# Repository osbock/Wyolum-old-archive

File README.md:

# Wyolum-old-archive aka the google code clockthree repo
This is an archive of the old Wyolum Google code repo.
New commits should not be made here.
See instead separate repositories under:
http://github.com/wyolum

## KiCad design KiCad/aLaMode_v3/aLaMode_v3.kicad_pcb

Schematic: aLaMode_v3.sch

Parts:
C1, C7, C14: 100n; c_0805
C8: 47u,10V; C_ELCO_SMD
C10, C11: 22p; c_0805
D3, D4: RB886G; d_VMD2
D8: MBRM110LT1G; do_457
DIP1: DIP
F2: nanoSMDC110F; f_1206
IC1: ATMEGA328-PU; DIP-28__300_ELL
P4: PWM_SERVO; Header_Servo
P5: 5V_SERVO; Header_Servo
P6: GND_SERVO; Header_Servo
P7: GPS_UP501; Header_GPS
P8: FTDI; Header_FTDI
P9: ICSP; Header_ICSP
P13: AREF; Header_A_REF
P14: ANALOG_5V0; Header_6x1
P15: ANALOG_GND; Header_6x1
R1, R2, R3, R4, R6, R7: 10k; r_0805
R15: 8k2; r_0805
R16: 16k; r_0805
SD1: SD_CARD_MICRO; SD_Micro
SHIELD1: ARDUINO_SHIELD; ARDUINO_SHIELD_2_040pins
SW1: RST; SW_SMD
U2: 74HC125; SO14E
X1: 16MHz; Xtal_SMD2

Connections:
+3.3V: C14.2, D3.1 (A), P7.4, P13.1, P14.4, P14.5, P14.6, R3.1, R4.1, R6.1, SD1.4, SHIELD1.3V3, U2.12 (D), U2.13 (E), U2.14 (VCC); also elsewhere on the board
/5V_INT: F2.2, P4.7, P4.8
/5V_SERVO: C8.1, D8.2 (K), P5.1, P5.2, P5.3, P5.4, P5.5, P5.6, P5.7, P5.8
/AREF: IC1.21 (AREF), P13.2, SHIELD1.AREF
/GPS_BAT: D3.2 (K), D4.2 (K), P7.5
/GPS_Rx: P7.1, R15.2, R16.1
/PB0: IC1.14 (PB0(ICP)), SHIELD1.8
/PB1: IC1.15 (PB1(OC1A)), P4.4, SHIELD1.9
/PB6: C10.1, IC1.9 (PB6(XTAL1/TOSC1)), X1.1
/PB7: C11.1, IC1.10 (PB7(XTAL2/TOSC2)), X1.2
/PC0: IC1.23 (PC0(ADC0)), SHIELD1.AD0
/PC1: IC1.24 (PC1(ADC1)), SHIELD1.AD1
/PC2: IC1.25 (PC2(ADC2)), SHIELD1.AD2
/PC3: IC1.26 (PC3(ADC3)), SHIELD1.AD3
/PD2_1pps: IC1.4 (PD2(INT0)), P7.6, SHIELD1.2
/PD4_GPS_Rx: IC1.6 (PD4(XCK/T0)), R15.1, SHIELD1.4
/PD5: IC1.11 (PD5(T1)), P4.2, SHIELD1.5
/PD6_GPS_Tx: IC1.12 (PD6(AIN0)), P4.3, P7.2, SHIELD1.6
/PD7: IC1.13 (PD7(AIN1)), SHIELD1.7
/RPi/5V0: C1.1, F2.1, IC1.7 (VCC), IC1.20 (AVCC), P9.2, P13.3, P14.1, P14.2, P14.3, R1.1, R2.1, R7.1, SHIELD1.5V; also elsewhere on the board
/RPi/MISO: IC1.18 (PB4(MISO)), P9.1, SD1.7, SHIELD1.12; also elsewhere on the board
/RPi/MOSI: IC1.17 (PB3(MOSI/OC2)), P4.6, P9.4, R4.2, SHIELD1.11, U2.5 (D); also elsewhere on the board
/RPi/RESET: C7.2, IC1.1 (PC6(/RESET)), P9.5, R7.2, SHIELD1.RST, SW1.2; also elsewhere on the board
/RPi/RXD: IC1.2 (PD0(RXD)), P8.4, SHIELD1.0; also elsewhere on the board
/RPi/SCK: IC1.19 (PB5(SCK)), P9.3, R6.2, SHIELD1.13, U2.2 (D); also elsewhere on the board
/RPi/SCL: IC1.28 (PC5(ADC5/SCL)), R1.2, SHIELD1.AD5; also elsewhere on the board
/RPi/SDA: IC1.27 (PC4(ADC4/SDA)), R2.2, SHIELD1.AD4; also elsewhere on the board
/RPi/TXD: IC1.3 (PD1(TXD)), P8.5, SHIELD1.1; also elsewhere on the board
/SD_CLK: SD1.5, U2.3 (O)
/SD_CS: SD1.2, U2.8 (O)
/SD_DATA_IN: SD1.3, U2.6 (O)
/SS: IC1.16 (PB2(SS/OC1B)), P4.5, R3.2, SHIELD1.10, U2.9 (D)
/aLaMode_pwr/USBVCC: P8.3; also elsewhere on the board
/aLaMode_pwr/V_IN: SHIELD1.V_IN; also elsewhere on the board
/aLaMode_rtc/BAT: D4.1 (A); also elsewhere on the board
/aLaMode_rtc/PD3_SQW: IC1.5 (PD3(INT1)), P4.1, SHIELD1.3; also elsewhere on the board
/~RTS: C7.1, P8.6
GND: C1.2, C8.2, C10.2, C11.2, C14.1, D8.1 (A), IC1.8 (GND), IC1.22 (AGND), P6.1, P6.2, P6.3, P6.4, P6.5, P6.6, P6.7, P6.8, P7.3, P8.1, P8.2, P9.6, P15.1, P15.2, P15.3, P15.4, P15.5, P15.6, R16.2, SD1.6, SD1.G1, SD1.G2, SD1.G3, SD1.G4, SHIELD1.GND1, SHIELD1.GND2, SHIELD1.GND3, SW1.1, U2.1 (E), U2.4 (E), U2.7 (GND), U2.10 (E); also elsewhere on the board

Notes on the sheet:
PD3 (SQW) RTC 1Hz signal
FTDI Header
ISP Header
EXT Mode : Connect EXT Servo supply to 5V_Servo and GND_SERVO Connectors Pins 7/8. INT Mode : Use jumper links to shunt Pins 7/8 of PWM_SERVO and 5V_SERVO connectors to run Servos using on board 5V.
SERVO Header
PWM6
PWM5
PWM4
PWM3
PWM2
PWM1
GPS Header
PD2 (1pps) GPS 1pps signal
5V to 3V level translation for GPS Rx signal. R16 may be replaced with 3V3 Zener Diode.

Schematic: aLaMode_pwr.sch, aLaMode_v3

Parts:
C2, C4: 100n; c_0805
C3: 2u2 Tant; c_0805
C5: 2u2; c_0805
C6: 100u,25V; C_ELCO_SMD
C15: 1n; c_0805
C16: 10n; c_0805
D1: 5V0; led_0805
D2: 3V3; led_0805
D5: MBRM110LT1G; do_457
D7: SMBJ5.0CA-TR; diode-DO214AA
D13: BLINK; led_0805
F1: nanoSMDC110F; f_1206
G1, G2: Logo_Wyolum; Logo-WL3
G3, G4: Logo_OH; OSHW_6mm
P10: V_IN; JACK_ALIM
P12: UUSB_B; USB_B_Micro
PCB1: PCB
Q1: FDN340P; SOT23-3
R5, R8: 1k5; r_0805
R10, R11: 10k; r_0805
R12: 1k; r_0805
R14: 0E; r_0805
U1: LP2985-33DBVR; SOT23-5
U3: NCP1117ST50T3G; SOT223
U5: LM358N; SO8E

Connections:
+3.3V: C5.1, R8.1, U1.5 (OUT), U5.2 (-); also elsewhere on the board
/RPi/5V0: C2.1, C3.1, C4.1, C15.1, D7.1, F1.2, Q1.S, R5.1, R14.2, U1.1 (IN), U1.3 (ON/~OFF), U3.2 (OUT), U3.4 (OUT), U5.8 (VCC); also elsewhere on the board
/RPi/SCK: U5.5 (+); also elsewhere on the board
/aLaMode_pwr/CMP: R10.2, R11.1, U5.3 (+)
/aLaMode_pwr/GATE_CMD: Q1.G, U5.1
/aLaMode_pwr/PWR_IN: D5.1 (A), P10.1 (+)
/aLaMode_pwr/USBVCC: Q1.D; also elsewhere on the board
/aLaMode_pwr/USB_IN: F1.1, P12.1 (5V_USB)
/aLaMode_pwr/V_IN: C6.1, D5.2 (K), R10.1, R14.1, U3.3 (IN); also elsewhere on the board
GND: C2.2, C3.2, C4.2, C5.2, C6.2, C15.2, C16.2, D1.2 (K), D2.2 (K), D7.2, D13.2 (K), P10.2 (-), P10.3 (S), P12.5 (GND), P12.T1, P12.T2, P12.T3, P12.T4, P12.T5, P12.T6, R11.2, U1.2 (GND), U3.1 (GND), U5.4 (GND); also elsewhere on the board
unnamed: C16.1, U1.4 (NC/FB)
unnamed: D1.1 (A), R5.2
unnamed: D13.1 (A), R12.2
unnamed: R12.1, U5.6 (-), U5.7
unnamed: D2.1 (A), R8.2

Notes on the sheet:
INDICATORS
BLINK LED - D13
USB<->Barrel Socket Auto Switch
BARREL POWER SOCKET
Micro USB-B POWER SOCKET
If using Micro USB -B socket, DO NOT INSTALL : P10, D5, U3 AND INSTALL Resistor R14 across pins 2 and 3 of U3 If using Barrel Socket, DO NOT INSTALL : P12, F1, D7, C15, R14
TE - 1981568-1 or FCI - 10118193-0001LF
Bi-directional clamping Diode, 5V
Polyswitch resettable fuse 1.1A Hold, 2.2A Trip 8V max.
DNP

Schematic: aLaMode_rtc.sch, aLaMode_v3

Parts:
B2, B3, B15: I/O
BT1: BATT_RTC; CR1632_2
C9: 100n; c_0805
R9: 10k; r_0805
U4: DS3231N; DS3231

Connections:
/RPi/5V0: R9.1, U4.2 (Vcc); also elsewhere on the board
/RPi/SCL: U4.16 (SCL); also elsewhere on the board
/RPi/SDA: U4.15 (SDA); also elsewhere on the board
/aLaMode_rtc/32k: B15.1, U4.1 (32KHz)
/aLaMode_rtc/BAT: BT1.+, C9.1, U4.14 (Vbat); also elsewhere on the board
/aLaMode_rtc/PD3_SQW: B2.1, R9.2, U4.3 (!(INT)/SQR); also elsewhere on the board
/aLaMode_rtc/RST: B3.1, U4.4 (!(Reset))
GND: BT1.-, C9.2, U4.5 (NC), U4.6 (NC), U4.7 (NC), U4.8 (NC), U4.9 (NC), U4.10 (NC), U4.11 (NC), U4.12 (NC), U4.13 (GND); also elsewhere on the board

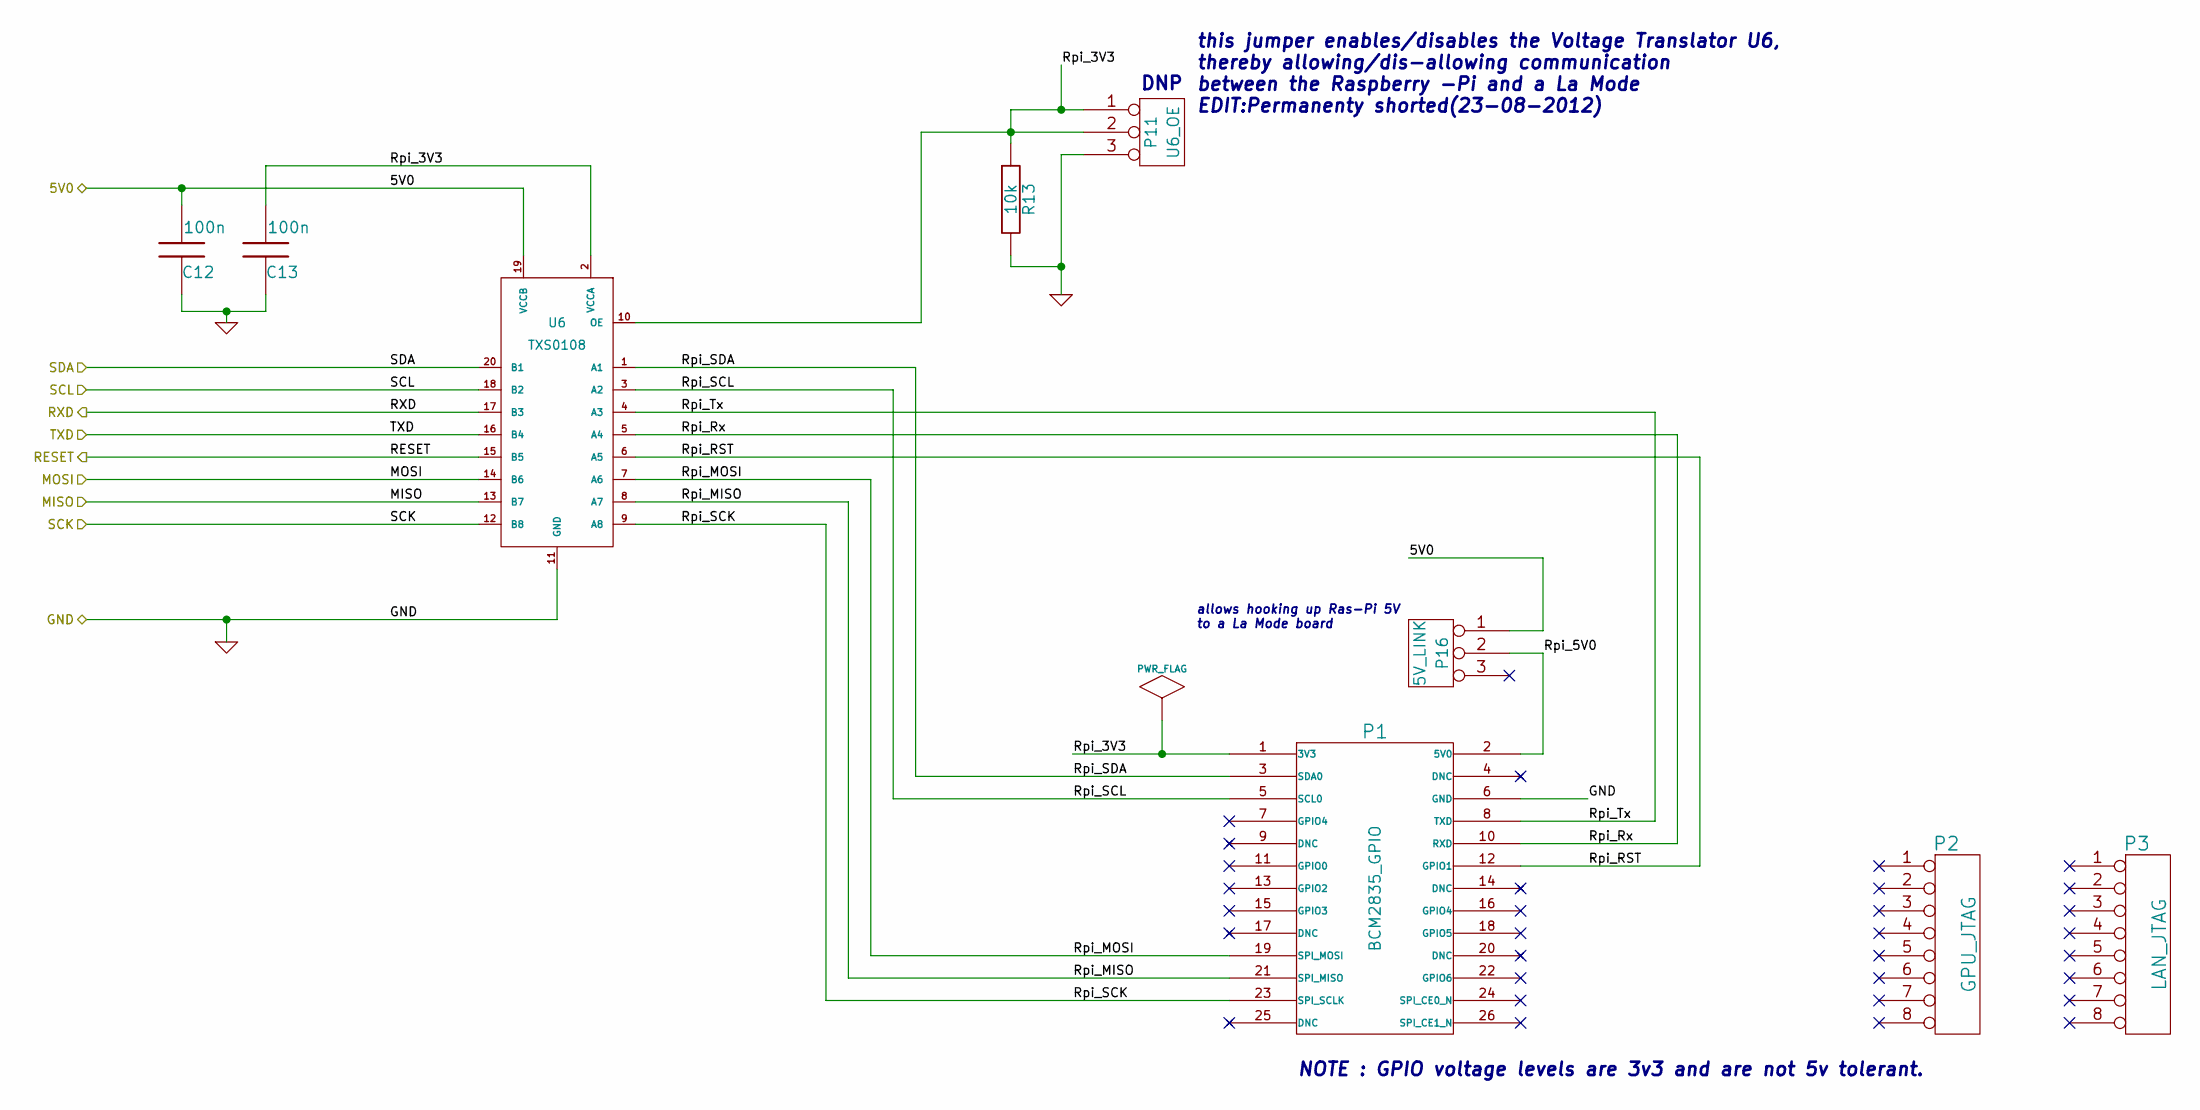
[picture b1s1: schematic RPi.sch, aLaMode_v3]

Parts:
C12, C13: 100n; c_0805
P1: BCM2835_GPIO; Header_GPIO
P2: GPU_JTAG; Header_GPU_JTAG
P3: LAN_JTAG; Header_GPU_JTAG
P11: U6_OE; Header_U6OE_SMT
P16: 5V_LINK; Header_U6OE_SMT
R13: 10k; r_0805
U6: TXS0108; tssop-20

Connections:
/RPi/5V0: C12.2, P16.1, U6.19 (VCCB); also elsewhere on the board
/RPi/MISO: U6.13 (B7); also elsewhere on the board
/RPi/MOSI: U6.14 (B6); also elsewhere on the board
/RPi/RESET: U6.15 (B5); also elsewhere on the board
/RPi/RXD: U6.17 (B3); also elsewhere on the board
/RPi/Rpi_3V3: C13.2, P1.1 (3V3), P11.1, P11.2, R13.1, U6.2 (VCCA), U6.10 (OE)
/RPi/Rpi_5V0: P1.2 (5V0), P16.2
/RPi/Rpi_MISO: P1.21 (SPI_MISO), U6.8 (A7)
/RPi/Rpi_MOSI: P1.19 (SPI_MOSI), U6.7 (A6)
/RPi/Rpi_RST: P1.12 (GPIO1), U6.6 (A5)
/RPi/Rpi_Rx: P1.10 (RXD), U6.5 (A4)
/RPi/Rpi_SCK: P1.23 (SPI_SCLK), U6.9 (A8)
/RPi/Rpi_SCL: P1.5 (SCL0), U6.3 (A2)
/RPi/Rpi_SDA: P1.3 (SDA0), U6.1 (A1)
/RPi/Rpi_Tx: P1.8 (TXD), U6.4 (A3)
/RPi/SCK: U6.12 (B8); also elsewhere on the board
/RPi/SCL: U6.18 (B2); also elsewhere on the board
/RPi/SDA: U6.20 (B1); also elsewhere on the board
/RPi/TXD: U6.16 (B4); also elsewhere on the board
GND: C12.1, C13.1, P1.6 (GND), P11.3, R13.2, U6.11 (GND); also elsewhere on the board

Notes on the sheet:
allows hooking up Ras-Pi 5V to a La Mode board
this jumper enables/disables the Voltage Translator U6, thereby allowing/dis-allowing communication between the Raspberry -Pi and a La Mode EDIT:Permanenty shorted(23-08-2012)
NOTE : GPIO voltage levels are 3v3 and are not 5v tolerant.
DNP

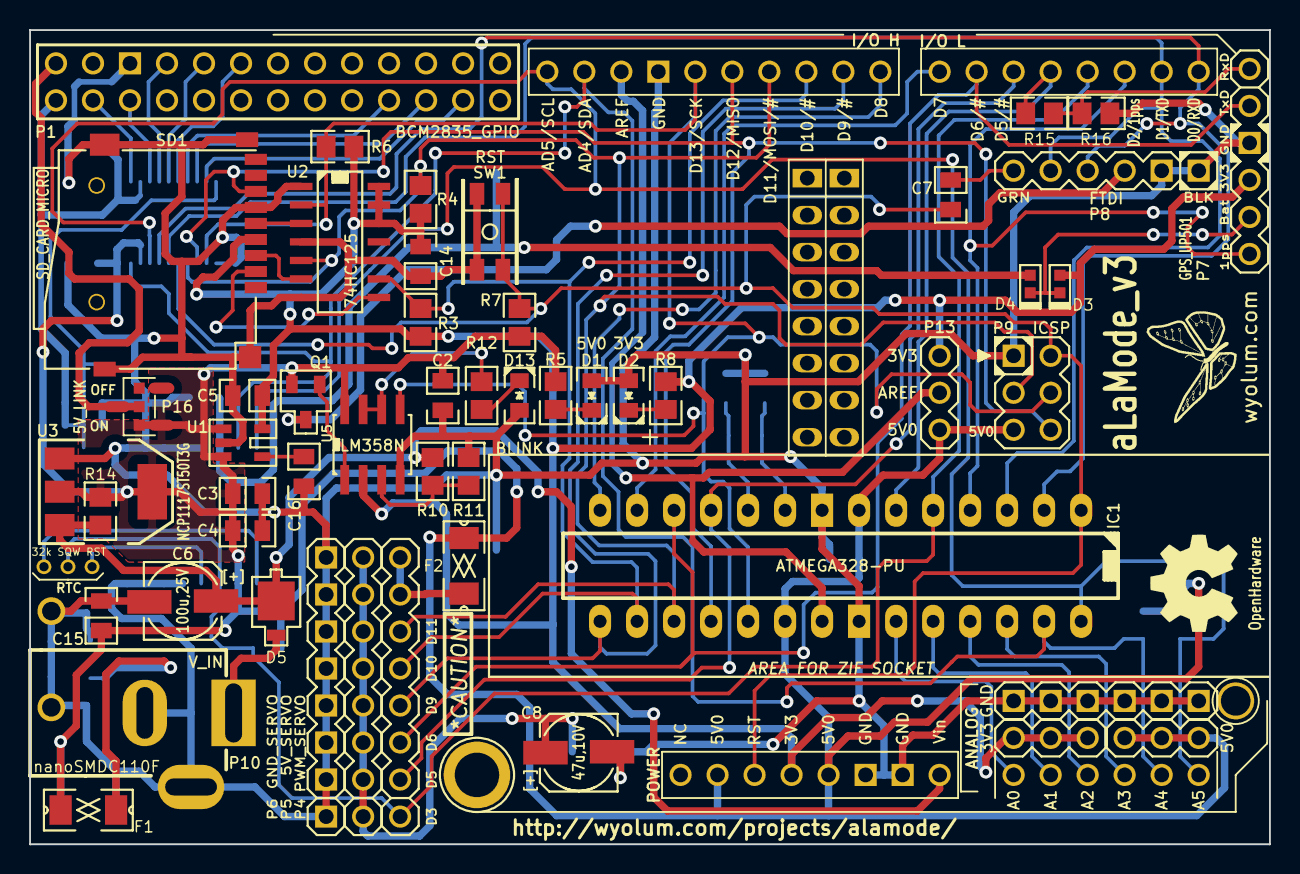
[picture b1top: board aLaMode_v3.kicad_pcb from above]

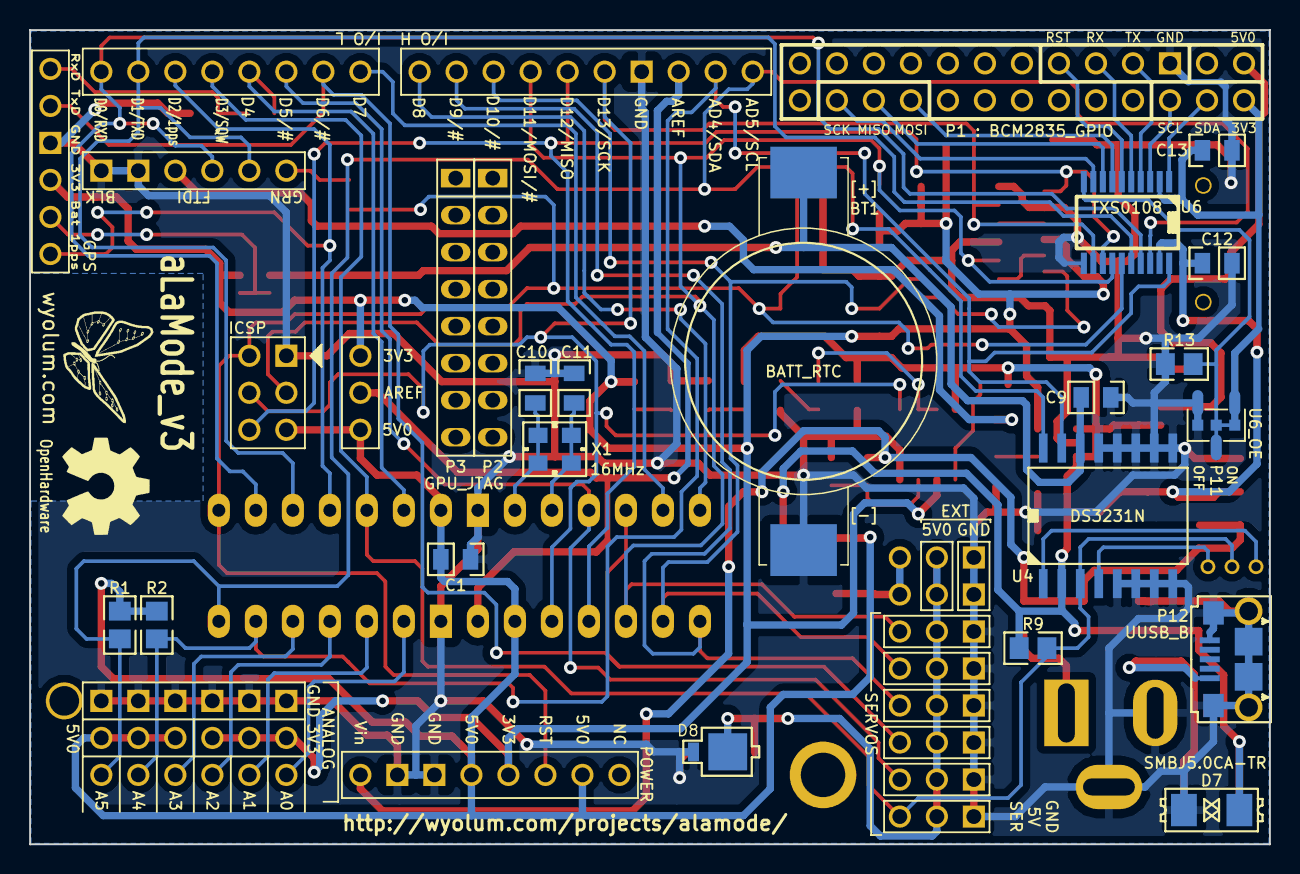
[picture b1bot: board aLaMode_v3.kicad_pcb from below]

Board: 2 copper layers, 85.1 x 55.9 mm, 80 parts (22 on the bottom side), 59 nets.

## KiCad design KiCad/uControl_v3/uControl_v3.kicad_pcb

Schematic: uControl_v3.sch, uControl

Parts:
B4, B12: PB0; I_O
B8: PC0; I_O
B9: PC1; I_O
B10: PC6; I_O
B11: PC7; I_O
C1, C4, C28, C43, C44: 100n; c_0805
C2, C3: 22p; c_0603
C42: 100u,16V; C_ELCO_SMD
P1: AREF; ShortLink2
P4: ICSP; Header_ISP
P5: FTDI; Header_FTDI
P23: Alt_Add; ShortLink2
P28: Int1; ShortLink2
P29: Int2; ShortLink2
R1, R2, R3, R21, R22: 10k; r_0805
SC1, SC2, SC3, SC4, SC5, SC6, SC7, SC8, SC9, SC10: SCREW; vite_3mm
SW1: Reset; SW_PB_V_H
SW2: INT0; SW_PB_V_H
SW3: INT1; SW_PB_V_H
U7: ATMEGA328-AU-ND; TQFP32
U11: ADXL345
X1: 16MHz; Xtal_SMD3

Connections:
+3.3V: C42.1 (+), C43.1, C44.1, P1.1, P23.3, P28.3, P29.3, U11.1 (VDD), U11.6 (VSS), U11.7 (CS); also elsewhere on the board
/ACL_INT1: P28.2, U11.8 (INT1)
/ACL_INT2: P29.2, U11.9 (INT2)
/ACL_SDO: P23.2, U11.12 (SDO)
/AREF: P1.2, U7.20 (AREF)
/BBB/5V0: C1.1, C28.1, P1.3, P4.2, R1.1, R2.1, R3.1, SW2.2, SW3.2, U7.4 (VCC), U7.6 (VCC), U7.18 (AVCC); also elsewhere on the board
/BBB/I2C1_SCL: U11.14 (SCL); also elsewhere on the board
/BBB/I2C1_SDA: U11.13 (SDA); also elsewhere on the board
/BBB/MISO: P4.1, U7.16 (PB4(MISO)); also elsewhere on the board
/BBB/RESET: C4.2, P4.5, R1.2, SW1.2, U7.29 (PC6(/RESET)); also elsewhere on the board
/BBB/RXD: P5.4, U7.30 (PD0(RXD)); also elsewhere on the board
/BBB/SCK: P4.3, U7.17 (PB5(SCK)); also elsewhere on the board
/BBB/SCL: R3.2, U7.28 (PC5(ADC5/SCL)); also elsewhere on the board
/BBB/SDA: R2.2, U7.27 (PC4(ADC4/SDA)); also elsewhere on the board
/BBB/TXD: P5.5, U7.31 (PD1(TXD)); also elsewhere on the board
/BBB/~MOSI: P4.4, U7.15 (PB3(MOSI/OC2)); also elsewhere on the board
/Interface/PC2_Pr2: U7.25 (PC2(ADC2)); also elsewhere on the board
/Interface/PC3_Pr1: U7.26 (PC3(ADC3)); also elsewhere on the board
/Interface/PD4_Valve2: U7.2 (PD4(XCK/T0)); also elsewhere on the board
/Interface/~PB1_Pump: U7.13 (PB1(OC1A)); also elsewhere on the board
/Interface/~PD5_Valve: U7.9 (PD5(T1)); also elsewhere on the board
/Interface/~PD6_Spk: U7.10 (PD6(AIN0)); also elsewhere on the board
/Interface/~SS: U7.14 (PB2(SS/OC1B)); also elsewhere on the board
/PB0: B12.1, U7.12 (PB0(ICP))
/PB6: C2.1, U7.7 (PB6(XTAL1/TOSC1)), X1.1
/PB7: C3.1, U7.8 (PB7(XTAL2/TOSC2)), X1.2
/PC0: B8.1, U7.23 (PC0(ADC0))
/PC1: B9.1, U7.24 (PC1(ADC1))
/PC6: B10.1, U7.19 (ADC6)
/PC7: B11.1, U7.22 (ADC7)
/PD2: R21.1, SW2.1, U7.32 (PD2(INT0))
/PD7: B4.1, U7.11 (PD7(AIN1))
/~PD3: R22.1, SW3.1, U7.1 (PD3(INT1))
/~RTS: C4.1, P5.6
GND: C1.2, C2.2, C3.2, C28.2, C42.2 (-), C43.2, C44.2, P4.6, P5.1, P5.2, P23.1, P28.1, P29.1, R21.2, R22.2, SW1.1, U7.3 (GND), U7.5 (GND), U7.21 (AGND), U11.2 (GND), U11.4 (GND1), U11.5 (GND2), U11.10 (GND3), X1.3; also elsewhere on the board

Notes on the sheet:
SW INT1 (ex Blank)
Mounting Holes
Pressure
CS #1 Pr Sensor
PUMP PWM (ex Pump ~PB1_IO_T)
Blank (ex Pump PB0_IO_R)
Blank (ex Pump PD7_IO_X)
Speaker PWM (ex Blank)
Valve #1 PWM
Valve #2 (ex Flow_Rx)
SW INT0 (ex Flow_Tx)
FTDI Header
ISP Header
Blank (ex Pulse)
Blank
Analog, from Absolute Pr Sensor
Analog, from Gage Pr Sensor
Accelerometer, 3V3 I2C

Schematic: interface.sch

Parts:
C5, C7, C8, C9, C10, C11, C12, C13, C14, C17, C29, C31: 100nF; c_0805
C27: 100uF; C_ELCO_SMD
D1, D3, D9: S1D-13-F; diode-DO214AC
M1: MANIFOLD
P7: GAGE_PR; HCEM500GUH9P3
P8: ABSO_PR; HDIB002AUY8H5
P9, P10: C3SB; pin_strip_4-90
P11: VSel_Vlv; Header_3
P14: X_VALVE; X_Valve_2
P15: Flow_Conn; Conn_Flow_SFM3000_Male
P16: FLOWMETER; FlowMeter_CFM3000
P17: PUMP; Pump_P54E01R_02
P18: Pump_Cable
P31: FLOW_CABLE
P34: VSel_Vlv2; Header_3
P38: X_VALVE2; X_Valve_2
Q1, Q2, Q3, Q4: BCP5416TA; SOT223
R4: 10k; r_0805
R5: 4k7; r_0805
R6: 1k; r_0805
SP1: BUZZER; Speaker
U1: TXB0104D

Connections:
+3.3V: C8.1, C10.1, P7.1, R4.2, U1.1 (VCCA), U1.8 (OE); also elsewhere on the board
/BBB/5V0: C5.2, C7.1, C9.1, C11.1, C12.2, C14.1, D3.2 (K), P8.1, P9.1, P10.1, P11.1, P15.2, P34.1, R5.1, R6.1, SP1.1, U1.14 (VCCB); also elsewhere on the board
/BBB/MISO: U1.13 (B1); also elsewhere on the board
/BBB/SCK: U1.12 (B2); also elsewhere on the board
/BBB/SCL: P8.6, P9.2, P10.2, P15.1; also elsewhere on the board
/BBB/SDA: P8.4, P9.3, P10.3, P15.4; also elsewhere on the board
/BBB/~MOSI: U1.10 (B4); also elsewhere on the board
/Interface/12V: C17.1, C27.1 (+), P11.3, P17.2, P34.3; also elsewhere on the board
/Interface/+Vlv: C13.1, D1.2 (K), P11.2, P14.1
/Interface/+Vlv2: C31.1, D9.2 (K), P34.2, P38.1
/Interface/-Vlv: D1.1 (A), P14.2 (PM), Q1.2 (C)
/Interface/-Vlv2: D9.1 (A), P38.2 (PM), Q3.2 (C)
/Interface/PC2_Pr2: P8.2; also elsewhere on the board
/Interface/PC3_Pr1: P7.3; also elsewhere on the board
/Interface/PD4_Valve2: Q3.1 (B); also elsewhere on the board
/Interface/P_MISO: P7.4, U1.2 (A1)
/Interface/P_MOSI: P7.8, U1.5 (A4)
/Interface/P_SCK: P7.5, U1.3 (A2)
/Interface/P_SS: P7.6, U1.4 (A3)
/Interface/Pump: C29.1, P17.4, R5.2
/Interface/Spk: D3.1 (A), Q4.2 (C), R6.2, SP1.2
/Interface/~PB1_Pump: Q2.1 (B); also elsewhere on the board
/Interface/~PD5_Valve: Q1.1 (B); also elsewhere on the board
/Interface/~PD6_Spk: Q4.1 (B); also elsewhere on the board
/Interface/~SS: U1.11 (B3); also elsewhere on the board
GND: C5.1, C7.2, C8.2, C9.2, C10.2, C11.2, C12.1, C13.2, C14.2, C31.2, P7.2, P8.3, P9.4, P10.4, P15.3, Q1.3 (E), Q2.3 (E), Q3.3 (E), Q4.3 (E), R4.1, U1.7 (GND); also elsewhere on the board
unnamed: C17.2, C27.2 (-), C29.2, P17.1, Q2.2 (C)

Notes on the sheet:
Flow Meter cable
Spare I2C on C3SB Bus
Pressure Sensor #2, Absolute, I2C Bus [HDIB002AUY8H5]
Valve #1 on digital PWM port either 12V (V_IN) or 5V0
Flow Meter, I2C , SFM3000 Address : 64 (h40)
Pressure Sensor #1, Gage, SPI Bus [HCEM500GUH9P3]
Pump, 12V DC [P54E01R] on digital port ~PB1
FlowMeter Footprint
Connector at uC_v2
Pump [P54E01R] Footprint
Pump cable
Valve #2 on digital port PD4 either 12V (V_IN) or 5V0
Speaker, 5V DC digital PWM port ~PD6
Valve Footprint
1 GND 2 12V 3 FG 4 PWM 5 NC

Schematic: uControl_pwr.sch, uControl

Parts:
C18, C20, C32, C34: 100nF; c_0805
C19, C33: 22uF X7R; c_1210
C21, C35: 3.3nF; c_0805
C22, C26, C36, C37: 100uF; C_ELCO_SMD
C30, C38: 10uF X7R; c_1206
D4: S1D-13-F; diode-DO214AC
D5: 5V0; led_0805
D6: 3V3; led_0805
D7: BLINK; led_0805
D8: 12V; led_0805
G1, G2: Logo_Wyolum; Logo-WL3
G3, G4: Logo_OH; OSHW_6mm
J1: 5V_EXT; Header_2
J2: 3V3_EXT; Header_2
L1, L2: 2u2H,3.0A; Inductor_SMD3; Mfr_PN XFL4020-222MEB, Coilcraft
P13: PWR_IN; Header_2
P24: PWR_IN; JACK_ALIM
PCB1: PCB
R7, R14: 100k; r_0805
R8: 330E; r_0805
R9: 120E; r_0805
R10, R13: 1k; r_0805
U3: TPS62133; TPS62132
U4: TPS62132

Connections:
+3.3V: C32.2, C33.1, J2.1, L2.2, R9.1, R14.2, U4.14 (VOS); also elsewhere on the board
/BBB/5V0: C18.2, C19.1, J1.1, L1.2, R7.2, R8.1, U3.14 (VOS); also elsewhere on the board
/BBB/SCK: R10.1; also elsewhere on the board
/Interface/12V: C20.2, C22.1, C26.1, C30.1, C34.2, C36.1, C37.1, C38.1, D4.2 (K), R13.1, U3.10 (AVIN), U3.11 (PVIN), U3.12 (PVIN), U3.13 (EN), U4.10 (AVIN), U4.11 (PVIN), U4.12 (PVIN), U4.13 (EN); also elsewhere on the board
/pwr/PWR_IN: D4.1 (A), P13.1, P24.1 (+)
GND: C18.1, C19.2, C20.1, C21.1, C22.2, C26.2, C30.2, C32.1, C33.2, C34.1, C35.1, C36.2, C37.2, C38.2, D5.2 (K), D6.2 (K), D7.2 (K), D8.2 (K), J1.2 (PM), J2.2 (PM), P13.2 (PM), P24.2 (-), P24.3 (S), U3.5 (FB), U3.6 (AGND), U3.7 (FSW), U3.8 (DEF), U3.15 (PGND), U3.16 (PGND), U4.5 (FB), U4.6 (AGND), U4.7 (FSW), U4.8 (DEF), U4.15 (PGND), U4.16 (PGND); also elsewhere on the board
unnamed: C21.2, U3.9 (SS/TR)
unnamed: L1.1, U3.1 (SW), U3.2 (SW), U3.3 (SW)
unnamed: R7.1, U3.4 (PG)
unnamed: D7.1 (A), R10.2
unnamed: D8.1 (A), R13.2
unnamed: D6.1 (A), R9.2
unnamed: D5.1 (A), R8.2
unnamed: C35.2, U4.9 (SS/TR)
unnamed: L2.1, U4.1 (SW), U4.2 (SW), U4.3 (SW)
unnamed: R14.1, U4.4 (PG)

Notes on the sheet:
5V0 Regulator for uControl
INDICATORS
BLINK LED - D13
BARREL POWER SOCKET
3V3 Regulator for uControl

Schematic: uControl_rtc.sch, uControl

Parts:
B1, B2, B3: I_O
BT1: BATT_HOLDER; CR2032
BT2: BATT_COIN
C23: 100nF; c_0805
R11: 10k; r_0805
U5: DS3231N; DS3231

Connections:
/BBB/5V0: R11.1, U5.2 (Vcc); also elsewhere on the board
/BBB/SCL: U5.16 (SCL); also elsewhere on the board
/BBB/SDA: U5.15 (SDA); also elsewhere on the board
/rtc/32k: B3.1, U5.1 (32KHz)
/rtc/BAT: BT1.+, C23.1, U5.14 (Vbat)
/rtc/RST: B2.1, U5.4 (!(Reset))
/rtc/SQR: B1.1, R11.2, U5.3 (!(INT)/SQR)
GND: BT1.-, C23.2, U5.5 (NC), U5.6 (NC), U5.7 (NC), U5.8 (NC), U5.9 (NC), U5.10 (NC), U5.11 (NC), U5.12 (NC), U5.13 (GND); also elsewhere on the board

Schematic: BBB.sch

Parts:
B5: 5V_ATMega; I_O
B6: 3V3_BBB; I_O
C39, C40, C41: 100n; c_0805
J3: addr; Header_2x2
P19: U6_OE; ShortLink2
P20: 5V_LINK; ShortLink2
P21, P22: CONN_23X2; PIN_ARRAY_23X2
Q5: 2N7002KW; SOT23-3
R12: 4k7; r_0805
R15, R26, R27: 10k; r_0805
R16, R17, R18, R23: 4k75; r_0805
R19, R20: 1k5; r_0805
R24, R25: 220; r_0805
SW4: PWR_BBB; SW_PB_V_H
SW5: GPIO1_6; SW_PB_V_H
SW6: GPIO1_29; SW_PB_V_H
U8: TSX0108; TXS0108EPWR
U9: CAT24C256; SO8E
U10: BEAGLEBONE

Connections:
/BBB/3V3_BBB: B6.1, Q5.S, R27.2
/BBB/5V0: C39.2, P20.1, R26.1, U8.19 (VCCB); also elsewhere on the board
/BBB/5V_ATMega: B5.1, Q5.D, R26.2
/BBB/A0: J3.3, R16.2, U9.1 (A0)
/BBB/A1: J3.1, R17.2, U9.2 (A1)
/BBB/A2: R18.2, U9.3 (A2)
/BBB/AIN0: P21.39, U10.C39 (AIN0)
/BBB/AIN1: P21.40, U10.C40 (AIN1)
/BBB/AIN2: P21.37, U10.C37 (AIN2)
/BBB/AIN3: P21.38, U10.C38 (AIN3)
/BBB/AIN4: P21.33, U10.C33 (AIN4)
/BBB/AIN5: P21.36, U10.C36 (AIN5)
/BBB/AIN6: P21.35, U10.C35 (AIN6)
/BBB/BBB_OE: P19.2, R15.1, U8.10 (OE)
/BBB/CLKOUT2: P21.41, U10.C41 (CLKOUT2)
/BBB/DGND_8: P22.1, P22.2, U10.B1 (DGND), U10.B2 (DGND)
/BBB/DGND_9_2: P21.43, P21.44, P21.45, P21.46, U10.C43 (DGND), U10.C44 (DGND), U10.C45 (DGND), U10.C46 (DGND)
/BBB/EHRPWM1A: P21.14, U10.C14 (EHRPWM1A)
/BBB/EHRPWM1B: P21.16, U10.C16 (EHRPWM1B)
/BBB/EHRPWM2A: P22.19, U10.B19 (EHRPWM2A)
/BBB/EHRPWM2B: P22.13, U10.B13 (EHRPWM2B)
/BBB/GNDA_ADC: P21.34, U10.C34 (GNDA_ADC)
/BBB/GPIO0_7: P21.42, U10.C42 (GPIO0_7)
/BBB/GPIO0_26: P22.14, U10.B14 (GPIO0_26)
/BBB/GPIO0_27: P22.17, U10.B17 (GPIO0_27)
/BBB/GPIO1_0: P22.25, U10.B25 (GPIO1_0)
/BBB/GPIO1_1: P22.24, U10.B24 (GPIO1_1)
/BBB/GPIO1_2: P22.5, U10.B5 (GPIO1_2)
/BBB/GPIO1_3: P22.6, U10.B6 (GPIO1_3)
/BBB/GPIO1_4: P22.23, U10.B23 (GPIO1_4)
/BBB/GPIO1_5: P22.22, U10.B22 (GPIO1_5)
/BBB/GPIO1_6: P22.3, U10.B3 (GPIO1_6)
/BBB/GPIO1_7: P22.4, U10.B4 (GPIO1_7)
/BBB/GPIO1_12: P22.12, U10.B12 (GPIO1_12)
/BBB/GPIO1_13: P22.11, U10.B11 (GPIO1_13)
/BBB/GPIO1_14: P22.16, U10.B16 (GPIO1_14)
/BBB/GPIO1_15: P22.15, U10.B15 (GPIO1_15)
/BBB/GPIO1_16: P21.15, U10.C15 (GPIO1_16)
/BBB/GPIO1_17: P21.23, U10.C23 (GPIO1_17)
/BBB/GPIO1_28: P21.12, U10.C12 (GPIO1_28)
/BBB/GPIO1_29: P22.26, R23.2, R25.1, U10.B26 (GPIO1_29)
/BBB/GPIO1_30: P22.21, U10.B21 (GPIO1_30)
/BBB/GPIO1_31: P22.20, U10.B20 (GPIO1_31)
/BBB/GPIO2_1: P22.18, U10.B18 (GPIO2_1)
/BBB/GPIO2_6: P22.45, U10.B45 (GPIO2_6)
/BBB/GPIO2_7: P22.46, U10.B46 (GPIO2_7)
/BBB/GPIO2_8: P22.43, U10.B43 (GPIO2_8)
/BBB/GPIO2_9: P22.44, U10.B44 (GPIO2_9)
/BBB/GPIO2_10: P22.41, U10.B41 (GPIO2_10)
/BBB/GPIO2_11: P22.42, U10.B42 (GPIO2_11)
/BBB/GPIO2_13: P22.40, U10.B40 (GPIO2_13)
/BBB/GPIO2_22: P22.27, U10.B27 (GPIO2_22)
/BBB/GPIO2_23: P22.29, U10.B29 (GPIO2_23)
/BBB/GPIO2_24: P22.28, U10.B28 (GPIO2_24)
/BBB/GPIO2_25: P22.30, U10.B30 (GPIO2_25)
/BBB/GPIO3_19: P21.27, U10.C27 (GPIO3_19)
/BBB/GPIO3_21: P21.25, U10.C25 (GPIO3_21)
/BBB/GPIO_12: P22.39, U10.B39 (GPIO2_12)
/BBB/I2C1_SCL: P21.17, U8.3 (A2), U10.C17 (I2C1_SCL); also elsewhere on the board
/BBB/I2C1_SDA: P21.18, U8.1 (A1), U10.C18 (I2C1_SDA); also elsewhere on the board
/BBB/I2C2_SCL: P21.19, R19.2, U9.6 (SCL), U10.C19 (I2C2_SCL)
/BBB/I2C2_SDA: P21.20, R20.2, U9.5 (SDA), U10.C20 (I2C2_SDA)
/BBB/MISO: U8.13 (B7); also elsewhere on the board
/BBB/PWR_BUT: P21.9, SW4.2, U10.C9 (PWR_BUT)
/BBB/RESET: U8.15 (B5); also elsewhere on the board
/BBB/RXD: U8.17 (B3); also elsewhere on the board
/BBB/SCK: U8.12 (B8); also elsewhere on the board
/BBB/SCL: U8.18 (B2); also elsewhere on the board
/BBB/SDA: U8.20 (B1); also elsewhere on the board
/BBB/SPI1_CS0: P21.28, U10.C28 (SPI1_CS0)
/BBB/SPI1_D0: P21.29, U8.8 (A7), U10.C29 (SPI1_D0)
/BBB/SPI1_D1: P21.30, U8.7 (A6), U10.C30 (SPI1_D1)
/BBB/SPI1_SCLK: P21.31, U8.9 (A8), U10.C31 (SPI1_SCLK)
/BBB/SYS_5V: P21.7, P21.8, U10.C7 (SYS_5V), U10.C8 (SYS_5V)
/BBB/SYS_RESETn: P21.10, U10.C10 (SYS_RESETn)
/BBB/TIMER4: P22.7, U10.B7 (TIMER4)
/BBB/TIMER5: P22.9, R12.2, R24.1, U10.B9 (TIMER5)
/BBB/TIMER6: P22.10, U8.6 (A5), U10.B10 (TIMER6)
/BBB/TIMER7: P22.8, U10.B8 (TIMER7)
/BBB/TXD: U8.16 (B4); also elsewhere on the board
/BBB/UART1_RXD: P21.26, U8.5 (A4), U10.C26 (UART1_RXD)
/BBB/UART1_TXD: P21.24, U8.4 (A3), U10.C24 (UART1_TXD)
/BBB/UART2_RXD: P21.22, U10.C22 (UART2_RXD)
/BBB/UART2_TXD: P21.21, U10.C21 (UART2_TXD)
/BBB/UART3_CTSN: P22.36, U10.B36 (UART3_CTSN)
/BBB/UART3_RTSN: P22.34, U10.B34 (UART3_RTSN)
/BBB/UART4_CTSN: P22.35, U10.B35 (UART4_CTSN)
/BBB/UART4_RTSN: P22.33, U10.B33 (UART4_RTSN)
/BBB/UART4_RXD: P21.11, U10.C11 (UART4_RXD)
/BBB/UART4_TXD: P21.13, U10.C13 (UART4_TXD)
/BBB/UART5_CTSN: P22.31, U10.B31 (UART5_CTSN)
/BBB/UART5_RTSN: P22.32, U10.B32 (UART5_RTSN)
/BBB/UART5_RXD: P22.38, U10.B38 (UART5_RXD)
/BBB/UART5_TXD: P22.37, U10.B37 (UART5_TXD)
/BBB/VDD_3V3EXP: C40.2, C41.1, P19.1, P21.3, P21.4, Q5.G, R12.1, R16.1, R17.1, R18.1, R19.1, R20.1, R23.1, R27.1, U8.2 (VCCA), U9.8 (VCC), U10.C3 (VDD_3V3EXP), U10.C4 (VDD_3V3EXP)
/BBB/VDD_5V: P20.2, P21.5, P21.6, U10.C5 (VDD_5V), U10.C6 (VDD_5V)
/BBB/VDD_ADC: P21.32, U10.C32 (VDD_ADC)
/BBB/~MOSI: U8.14 (B6); also elsewhere on the board
GND: C39.1, C40.1, C41.2, J3.2, J3.4, P19.3, P21.1, P21.2, R15.2, SW4.1, SW5.1, SW6.1, U8.11 (GND), U9.4 (GND), U10.C1 (DGND), U10.C2 (DGND); also elsewhere on the board
unnamed: R24.2, SW5.2
unnamed: R25.2, SW6.2

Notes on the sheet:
allows linking BBB 5V to uC_v3 5V
Enable/Disable U6 for comm betn BBB & uC_v3
LEVEL TRANSLATOR ATMega (5V) <> BBB (3V3)
Discrete LEVEL TRANSLATOR ATMega (5V) <> BBB (3V3)
(can use for SPI Select betn ATMega <> BBB)
BBB Buttons General purpose
BBB I2C for Accelerometer

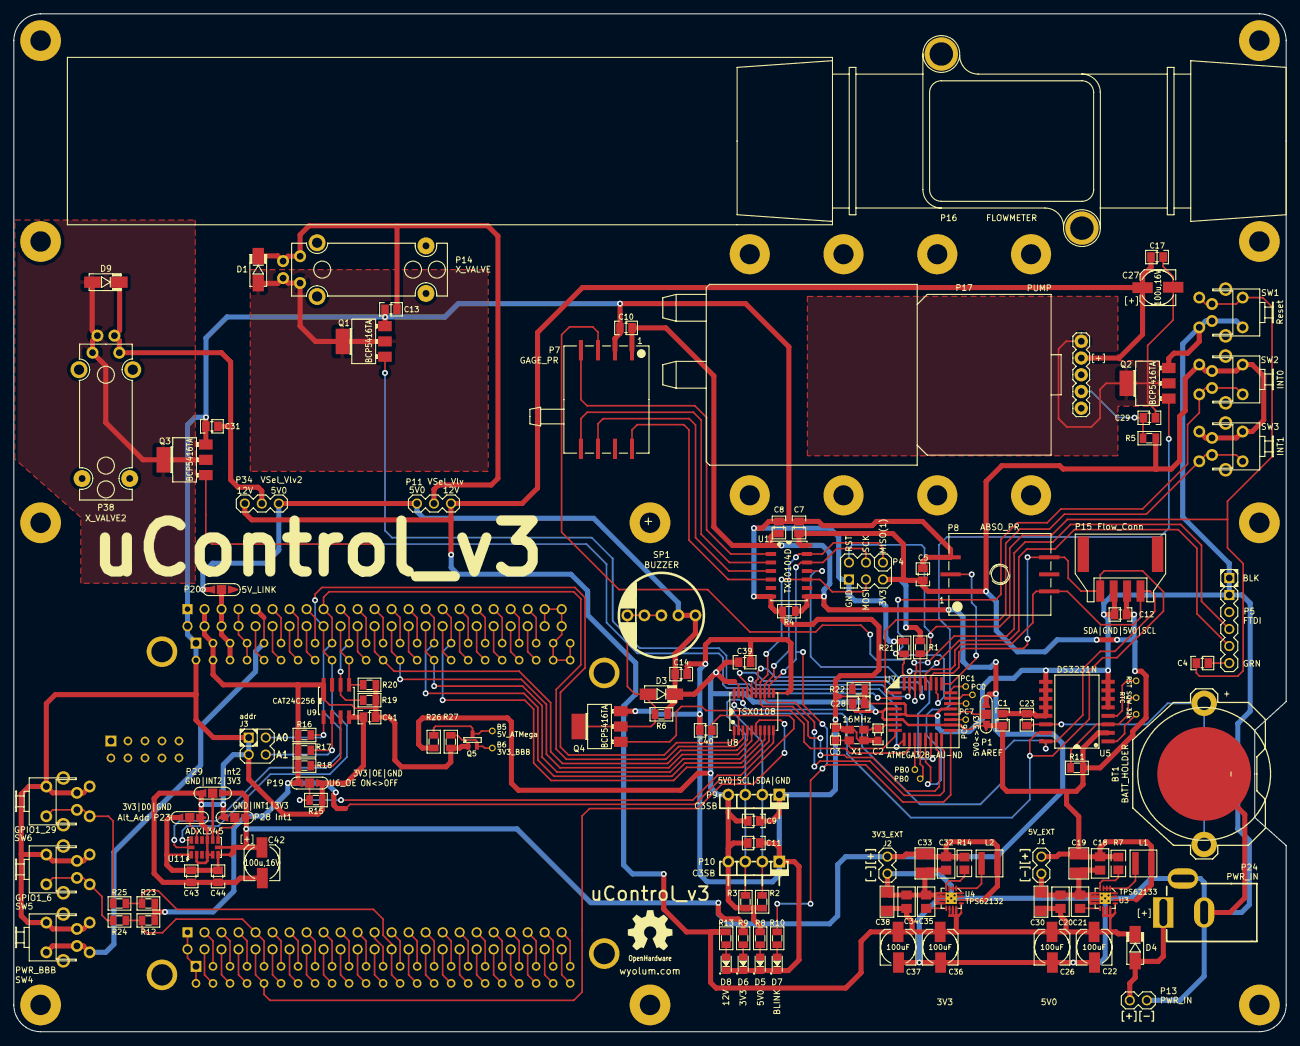
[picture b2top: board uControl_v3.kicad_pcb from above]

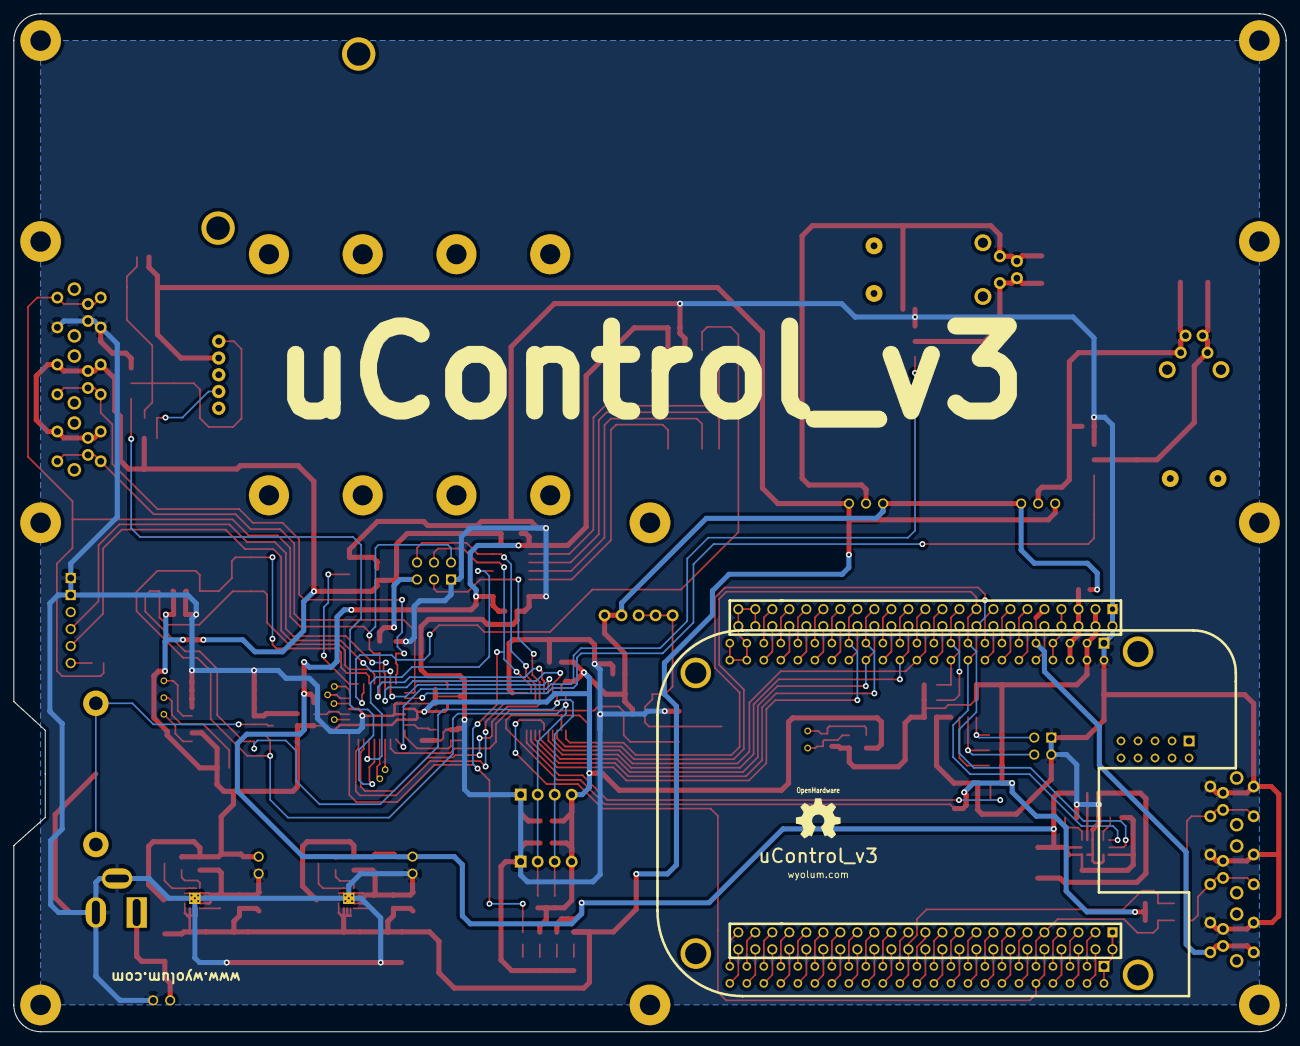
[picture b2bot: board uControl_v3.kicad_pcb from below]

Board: 2 copper layers, 190.0 x 152.0 mm, 149 parts (4 on the bottom side), 151 nets.

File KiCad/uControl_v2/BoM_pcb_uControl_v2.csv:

"Id";"Designator";"Package";"Quantity";"Designation";"Supplier and ref";
1;"P10,P9";"pin_strip_4-90";2;"C3SB";;;
2;"PCB1";"PCB";1;"PCB";;;
3;"SC8,SC9,SC10,SC7,SC3,SC4,SC2,SC6,SC5,SC1";"vite_3mm";10;"SCREW";;;
4;"P24";"JACK_ALIM";1;"PWR_IN";;;
5;"U5";"DS3231";1;"DS3231N";;;
6;"U6";"TXS0108EPWR";1;"TSX0108";;;
7;"P8";"HDIB002AUY8H5";1;"ABSO_PR";;;
8;"U1";"TXB0104D";1;"TXB0104D";;;
9;"P5";"Header_FTDI";1;"FTDI";;;
10;"SW1";"SW_PB_V_H";1;"Reset";;;
11;"BT1";"CR2032";1;"BATT_HOLDER";;;
12;"SW2";"SW_PB_V_H";1;"INT0";;;
13;"SW3";"SW_PB_V_H";1;"INT1";;;
14;"SP1";"Speaker";1;"BUZZER";;;
15;"R22,R21,R11,R1,R2,R3,R4,R12";"r_0603";8;"10k";;;
16;"C27,C19,C26,C6";"C_ELCO_SMD";4;"100u,16V";;;
17;"R6,R10,R13";"r_0603";3;"1k";;;
18;"R8";"r_0603";1;"330E";;;
19;"R9";"r_0603";1;"120E";;;
20;"P15";"Conn_Flow_SFM3000_Male";1;"Flow_Conn";;;
21;"D8";"led_0805";1;"12V";;;
22;"C22,C18";"c_0805_pol";2;"2u2 Tant";;;
23;"D4,D1,D3,D2,D9";"diode-DO214AC";5;"1N4007";;;
24;"P11";"Header_3";1;"VSel_Vlv";;;
25;"U7";"TQFP32";1;"ATMEGA328-AU-ND";;;
26;"C1,C4,C5,C7,C8,C9,C10,C11,C13,C17,C20,C21,C23,C24,C25,C14,C15,C16,C31,C28,C12,C29";"c_0603";22;"100n";;;
27;"C2,C3";"c_0603";2;"22p";;;
28;"D5";"led_0805";1;"5V0";;;
29;"D6";"led_0805";1;"3V3";;;
30;"D7";"led_0805";1;"BLINK";;;
31;"U2";"ADXL345";1;"ADXL345";;;
32;"P34";"Header_3";1;"VSel_Vlv2";;;
33;"P4";"Header_ISP";1;"ICSP";;;
34;"P16";"FlowMeter_CFM3000";1;"FLOWMETER";;;
35;"P7";"HCEM500GUH9P3";1;"GAGE_PR";;;
36;"X1";"Xtal_SMD3";1;"16MHz";;;
37;"P26";"ShortLink2";1;"5V_LINK";;;
38;"P25";"ShortLink2";1;"U6_OE";;;
39;"P2";"ShortLink2";1;"Alt_Add";;;
40;"P3";"ShortLink2";1;"Int1";;;
41;"P6";"ShortLink2";1;"Int2";;;
42;"Q4,Q3,Q2,Q1";"SOT223";4;"BCP5416TA";;;
43;"U3";"NCP1117ST50";1;"NCP1117ST50T3G";;;
44;"U4";"NCP1117ST33";1;"NCP1117ST33T3G";;;
45;"P27";"Header_GPIO";1;"BCM2835_GPIO";;;
46;"B4,B12";"I_O";2;"PB0";;;
47;"B1,B2,B3";"I_O";3;"I_O";;;
48;"B8";"I_O";1;"PC0";;;
49;"B9";"I_O";1;"PC1";;;
50;"B10";"I_O";1;"PC6";;;
51;"B11";"I_O";1;"PC7";;;
52;"P12";"PiPower";1;"PIPOWER";;;
53;"P13";"Header_2";1;"PWR_IN";;;
54;"P1";"ShortLink2";1;"AREF";;;
55;"P14";"X_Valve_2";1;"X_VALVE";;;
56;"P38";"X_Valve_2";1;"X_VALVE2";;;
57;"R5";"r_0603";1;"4k7";;;
58;"P17";"Pump_P54E01R_02";1;"PUMP";;;
59;"G4,G3";"OSHW_6mm";2;"Logo_OH";;;

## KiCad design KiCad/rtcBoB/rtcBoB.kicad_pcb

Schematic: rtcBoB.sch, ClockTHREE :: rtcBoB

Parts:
BT1: BATT_RTC; CR2032
C1: 100n; C2
H1, H2, H3, H4: CONN_1; vite_2mm5
P1: CDOT1; SCK-04-F-SMT
P2: CDOT2; SCK-04-F-SMT
P3: CONN_2; pin_strip_2
R1, R2, R3: 10k; rc03_vert
U1: DS3231; CR2032

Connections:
/32k: P1.2, R3.2, U1.1 (32KHz)
/BAT: C1.1, P1.1, P3.2 (PM), U1.14 (Vbat)
/RST: P1.4, R2.2, U1.4 (!(Reset))
/SCL: P2.2, U1.16 (SCL)
/SDA: P2.1, U1.15 (SDA)
/SQW: P1.3, R1.2, U1.3 (!(INT)/SQR)
/VCC: P2.3, R1.1, R2.1, R3.1, U1.2 (Vcc)
GND: BT1.-, C1.2, P2.4, U1.5 (NC), U1.6 (NC), U1.7 (NC), U1.8 (NC), U1.9 (NC), U1.10 (NC), U1.11 (NC), U1.12 (NC), U1.13 (GND)
unnamed: BT1.+, P3.1

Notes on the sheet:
Mounting Holes
rtcBOB
